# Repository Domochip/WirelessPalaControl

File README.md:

# WPalaControl

This project uses "Palazzetti library" and a D1 Mini to control Fumis based stove.  
It allows to power On/Off, change the setPoint, change fans speed, get status/alarms/temperatures of the stove.

Native HTTP requests are available which make is fully compatible with all existing Palazzetti/Fumis home automation plugins/apps.

Additionally, this project add MQTT protocol to monitor/control your stove in a much more efficient way.

## Stove Compatibility

Fumis Controller is used by many manufacturer for their stoves.
Here is a non-exhaustive list:  
  
Palazzetti / Jotul / TurboFonte / Godin / Fonte Flamme / Invicta / Casatelli / Alpis / Faizen / HETA / ...

If you have this control panel and/or controller in your stove, it's compatible.  

## Home Automation compatibility

|  | [MQTT Integration](https://www.home-assistant.io/integrations/mqtt/) (autodiscovery) |  |
| ------------- | ------------- | ------------- |
|  | [Palazzetti plugin](https://www.jeedom.com/market/index.php?v=d&p=market_display&id=3104) |  |

## Make/Get your adapter

🔧 If you want to build it yourself, you can find all details here : [BUILD](BUILD.md) 🔧  

🛍️🚀 Otherwise, I'm producing some small batches and offering it ready to use here :   

## Connect

⚠️ **You need to use a crossed RJ11 phone cable like this:** ⚠️  

Most of stove have an RJ11/RJ12 connector for PalaControl connection.  
If you don't have it, you need to cable it using a splitter to connect screen and PalaControl at the same time :  

Splitter and additional cable can be found on Aliexpress (search for "6p6c splitter" and "rj12 cable").  
The splitter should correspond to this small schematic :  

## First Boot

During First Boot, the ESP boot in Access Point Mode

- Network SSID : `WirelessPalaControlXXXX`
- Password : `PasswordPalaControl`
- ESP URL : 👉 http://wpalacontrol.local 👈

Connect to this network and then configure it.

## Configuration pages

### Status

It returns you useful informations about the module and the stove.  
**The stove SN appears then 1 minute later, refreshed stove information appears (default upload period)**  

### Config

#### System

- **Reboot**: restart the module
- **Reboot in Rescue Mode**: restart the module with default configuration

#### WiFi

- **ssid & password**: IDs of your Wifi Network  
- **hostname**: name of ESP on the network  
- **IP,GW,NetMask,DNS1&2**: Fixed IP configuration  

#### PalaControl - Home Automation

- **Type**: enable/disable MQTT communication  
- **Upload Period**: delay between refresh of stove information (in seconds)  
- **Hostname,Port,Username,Password**: MQTT server infos (username and password are - optional)  
- **Base Topic**: prefix used for WPalaControl topic structure  
- **MQTT Type**: defines MQTT topics and data structure: 
  - **Generic**: publish raw values under the base topic (e.g. "{baseTopic}/T1" = "*20.00*")
  - **Generic JSON**: publish values JSON to "category" topic under base topic (e.g. "{baseTopic}/TMPS" = "*{"INFO":{"CMD":"GET TMPS","RSP":"OK......*")
  - **Generic Categorized**: publish raw values to "category" topic under base topic (e.g. "{baseTopic}/TMPS/T1" = "*20.00*")
- **Home Assistant Discovery**: Enable/disable Home Assistant auto-discovery

### Firmware

It allows you to flash a new firmware version using `WPalaControl.*.bin` file:  

## Use it

### HTTP

Natively, HTTP GET request can be sent directly to the module.  
Syntax:  **http://wpalacontrol.local/cgi-bin/sendmsg.lua?cmd={command}**

### MQTT

Commands can be sent via MQTT to %BaseTopic%**/cmd** topic once MQTT is configured.  
Execution result is:

- published following the configured MQTT Type
- published on %BaseTopic%**/result** in JSON format 

Module connection status is published to %BaseTopic%**/connected**:

- 0: not connected
- 1: Module connected but no communication with the stove
- 2: Module and stove connected

### Command List
  
- `GET+STDT`: get static data
- `GET+ALLS`: get all status data
- `GET+STAT`: get status of the stove⏲️
- `GET+TMPS`: get temperatures of the stove⏲️
- `GET+FAND`: get Fan values⏲️
- `GET+SETP`: get current Set Point (desired temperature)⏲️
- `GET+POWR`: get current power (1-5)⏲️
- `GET+CUNT`: get some counters
- `GET+CNTR`: get some counters (same as GET+CUNT)⏲️
- `GET+DPRS`: get delta pressure data⏲️
- `GET+TIME`: get stove clock data⏲️
- `GET+IOPT`: get IO ports status
- `GET+SERN`: get stove Serial Number
- `GET+MDVE`: get stove model and fw version
- `GET+CHRD`: get chrono data
- `GET+PARM+92`: get parameter (ex : 92=pellet type (1-3))
- `GET+HPAR+57`: get hidden parameter (ex : 57=% of pellet to feed for pellet type 3)
- `BKP+PARM+CSV`: get all parameters in a CSV file (HTTP only) ✨
- `BKP+PARM+JSON`: get all parameters in a JSON file (HTTP only) ✨
- `BKP+HPAR+CSV`: get all hidden parameters in a CSV file (HTTP only) ✨
- `BKP+HPAR+JSON`: get all hidden parameters in a JSON file (HTTP only) ✨
- `CMD+ON`: turn stove ON
- `CMD+OFF`: turn stove OFF
- `SET+POWR+3`: set power (1-5)
- `SET+PWRU`: increase power by 1 unit
- `SET+PWRD`: decrease power by 1 unit
- `SET+SETP+20`: set Set Point (desired temperature)
- `SET+STPF+19.8`: set Set Point with a 0.2° precision (depend of your stove model)✨
- `SET+STPU`: increase Set Point by 1 unit
- `SET+STPD`: decrease Set Point by 1 unit
- `SET+RFAN+7`: set Room Fan value (0-5;6=Max;7=Auto)
- `SET+FN2U`: increase Room Fan by 1 unit
- `SET+FN2D`: decrease Room Fan by 1 unit
- `SET+FN3L+0`: set Room Fan 3 value (0-5)
- `SET+FN4L+0`: set Room Fan 4 value (0-5)
- `SET+SLNT+0`: set Silent mode value (0-1)
- `SET+TIME+2023-12-28+19:42:00`: set stove Date and Time (2000-2099) (1-12) (1-31) (0-23) (0-59) (0-59)
- `SET+CSST+0`: set Chrono Status value (0-1)
- `SET+CSTH+2+18`: set Chrono Program Start Hour (1-6) (0-23)
- `SET+CSTM+2+30`: set Chrono Program Start Minute (1-6) (0-59)
- `SET+CSPH+2+22`: set Chrono Program Stop Hour (1-6) (0-23)
- `SET+CSPM+2+45`: set Chrono Program Stop Minute (1-6) (0-59)
- `SET+CSET+2+19`: set Chrono Program Set Point (1-6) (desired temperature)
- `SET+CDAY+7+3+6`: set Chrono Program for week day (Day-Mem-Prog) (1-7) (1-3) (1-6)
- `SET+CPRD+1+19+18+30+22+45`: set Chrono Program data (Prog-Temp-StartH-StartM-StopH-StopM) (1-6) (temperature) (0-23) (0-59) (0-23) (0-59)
- `SET+PARM+92+2`: set parameter 92 to value 2 (ex : 92=pellet type (1-3))
- `SET+HPAR+57+95`: set hidden parameter 57 to value 95 (ex : 57=% of pellet to feed for pellet type 3)

⏲️: Published automatically  
✨: WPalaControl specific commands

### Description

MQTT infos published every "Upload Period":

- `STATUS`: status of the stove
- `LSTATUS`: status of the stove
- `T1`, `T2`, `T3`, `T4`, `T5`: temperature of the stove
- `F1V`, `F2V`, `F2L`, `F2LF`, `F3L`, `F4L`: fan values (meaning depend of your stove model)
- `IGN`: ignition counter
- `IGNERRORS`: ignition error counter
- `POWERTIME`: total heating time (hour:minute)
- `HEATTIME`: ??? (hour:minute)
- `SERVICETIME`: heating time since last maintenance (hour:minute)
- `ONTIME`: time from last power ON (hour:minute)
- `OVERTMPERRORS`: overtemperature error counter
- `STOVE_DATETIME`: date of the stove
- `STOVE_WDAY`: week day of the stove
- `SETP`: current Set Point (desired temperature)
- `PQT`: wood pellet consumption
- `PWR`: current power (1-5)
- `FDR`: feeder
- `DP_TARGET`: delta pressure target
- `DP_PRESS`: actual delta pressure

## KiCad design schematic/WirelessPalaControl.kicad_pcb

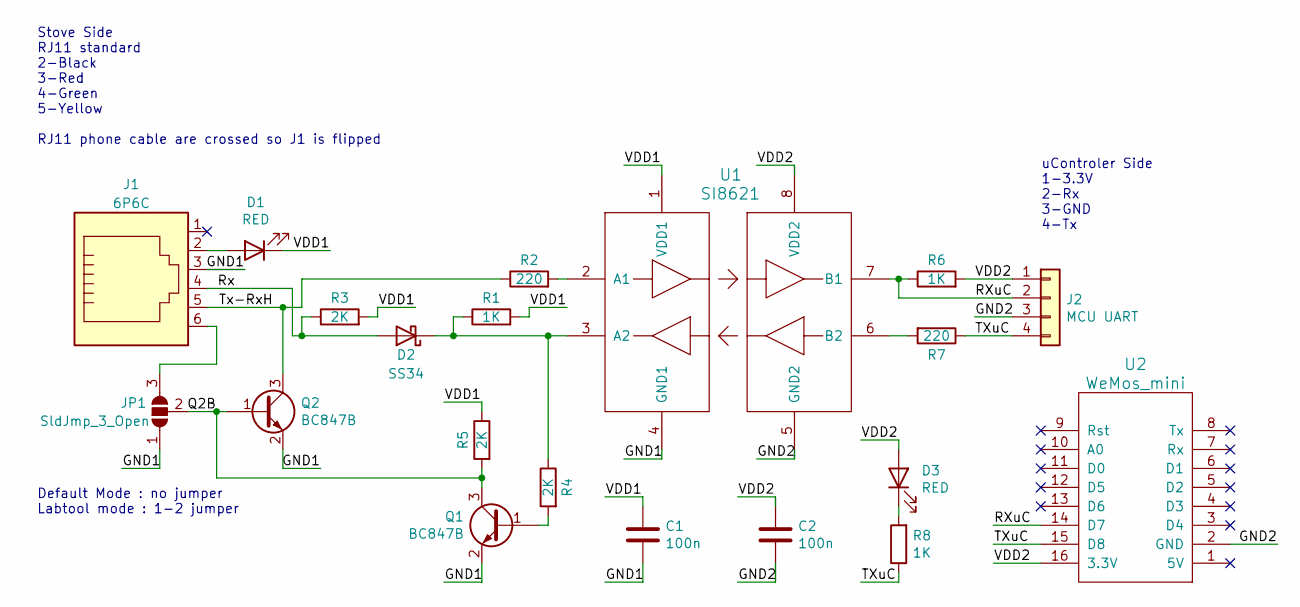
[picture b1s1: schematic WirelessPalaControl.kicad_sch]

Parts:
C1, C2: 100n; C_0805_2012Metric_Pad1.15x1.40mm_HandSolder
D1, D3: RED; LED_0805_2012Metric_Pad1.15x1.40mm_HandSolder
D2: SS34; D_SMA
J1: 6P6C; Ali_RJ12
J2: MCU UART; PinHeader_1x04_P2.54mm_Vertical
JP1: SldJmp_3_Open; SolderJumper-3_P1.3mm_Open_Pad1.0x1.5mm_NumberLabels
Q1, Q2: BC847B; SOT-23_Handsoldering
R1, R6, R8: 1K; R_0805_2012Metric_Pad1.15x1.40mm_HandSolder
R2, R7: 220; R_0805_2012Metric_Pad1.15x1.40mm_HandSolder
R3, R4, R5: 2K; R_0805_2012Metric_Pad1.15x1.40mm_HandSolder
U1: SI8621; SOIC-8_3.9x4.9mm_P1.27mm
U2: WeMos_mini; wemos-d1-mini-DIL-only

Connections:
/GND1: C1.2, J1.3, JP1.1 (A), Q1.2 (E), Q2.2 (E), U1.4 (GND1)
/GND2: C2.2, J2.3, U1.5 (GND2), U2.2 (GND)
/Q2B: JP1.2 (C), Q1.3 (C), Q2.1 (B), R5.2
/RXuC: J2.2, R6.1, U1.7 (B1), U2.14 (D7)
/Rx: D2.2 (A), J1.4, R3.1
/TXuC: J2.4, R7.1, R8.1, U2.15 (D8)
/Tx-RxH: J1.5, Q2.3 (C), R2.1
/VDD1: C1.1, D1.1 (K), R1.2, R3.2, R5.1, U1.1 (VDD1)
/VDD2: C2.1, D3.2 (A), J2.1, R6.2, U1.8 (VDD2), U2.16 (3.3V)
unnamed: D1.2 (A), J1.2
unnamed: D2.1 (K), R1.1, R4.1, U1.3 (A2)
unnamed: D3.1 (K), R8.2
unnamed: J1.6, JP1.3 (B)
unnamed: Q1.1 (B), R4.2
unnamed: R2.2, U1.2 (A1)
unnamed: R7.2, U1.6 (B2)

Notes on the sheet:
uControler Side 1-3.3V 2-Rx 3-GND 4-Tx
Default Mode : no jumper Labtool mode : 1-2 jumper
Stove Side RJ11 standard 2-Black 3-Red 4-Green 5-Yellow RJ11 phone cable are crossed so J1 is flipped

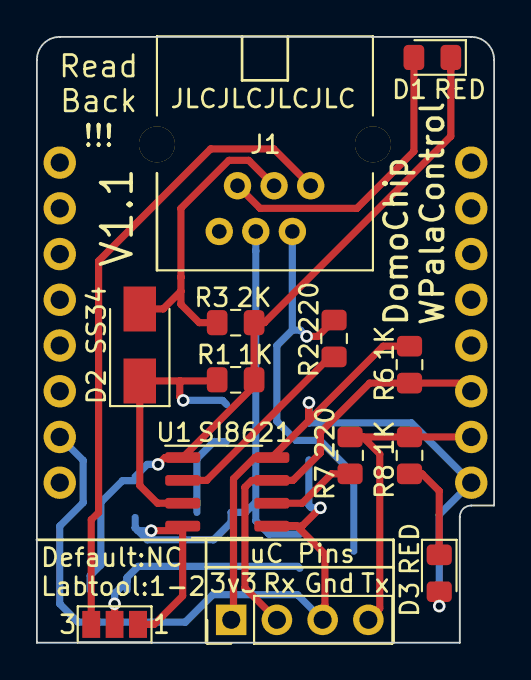
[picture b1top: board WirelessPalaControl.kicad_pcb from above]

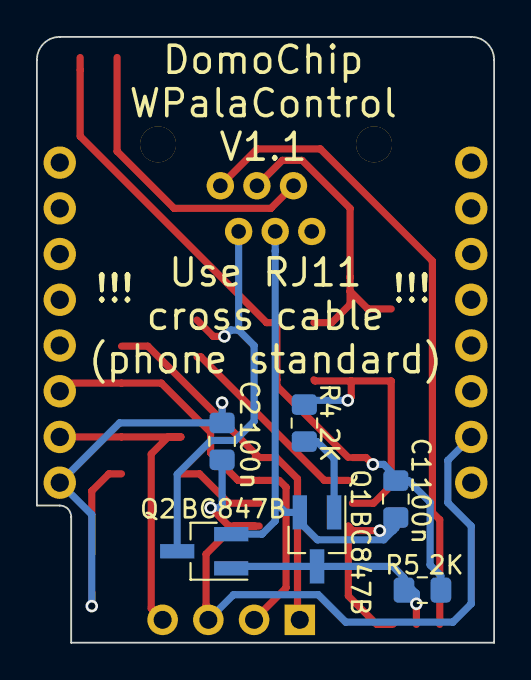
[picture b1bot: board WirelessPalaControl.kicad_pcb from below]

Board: 2 copper layers, 25.4 x 33.7 mm, 20 parts (7 on the bottom side), 16 nets.

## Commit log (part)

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2022-06-20 Add eventSourceOnly param to publishTick()
2022-06-20 split stove reading and MQTT code in publishTick
2022-06-20 Invert event subscription and get status
2022-06-20 improve comment
2022-06-20 Enable publishTicker even without HA
2022-06-20 Invert back event subscription and get status
2022-06-20 Remove eventSourceOnly param to publishTick()
2022-06-20 Add SN during generateStatusJSON()
2022-06-20 Update images
2022-06-20 Bump version to 2.1.1
2023-11-19 Fix version of ArduinoJson lib temporarily
2023-11-19 Ensure correct float rendering
2023-11-19 Use more ArduinoJson in executePalaCmd
2023-11-19 move "cmdProcessed = true"
2023-11-19 Formatting
2023-11-19 move DynJson out of executePalaCmd
2023-11-19 Use AsyncResponseStream to send json back
2023-11-20 return SUCCESS from jsonDoc
2023-11-21 optimize publishTick
2023-11-22 send event to web client in executePalaCmd
2023-11-22 return boolean instead of SUCCESS
2023-11-22 new publishTick using executePalaCmd
2023-11-23 Improved copy_base.py
2023-11-23 Improved prepare_webfiles.py
2023-11-24 comments and rename
2023-11-24 Add publishDataToMqtt method
2023-11-24 write first version of publishDataToMqtt
2023-11-24 use publishDataToMqtt in publishTick
2023-11-25 Add esp8266_exception_decoder
2023-12-03 Add log during init
2023-12-09 Switch LOG_SERIAL to 38400 for simplicity
2023-12-09 Switch monitor_speed to 38400
2023-12-09 Fix Stack issue by passing the whole jsonDoc
2023-12-09 Use the last ArduinoJson library
2023-12-09 Fix GET LABL result
2023-12-09 mqttCallback is able to process any comand
2023-12-09 Add more HA_MQTT type
2023-12-09 HA_MQTT_GENERIC_JSON is now default one
2023-12-09 Add MQTT type to UI
2023-12-10 Factorize publishTick
2023-12-10 publish accordingly to MQTT Generic type
2023-12-12 Add SET TIME comand
2023-12-12 move CMD answer fillin
2023-12-12 Add RSP ERROR answers
2023-12-12 code simplification for GET PARM
2023-12-12 revert code simplification for GET PARM
2023-12-14 Remove .vscode folder
2023-12-14 Ignore the whole .vscode folder
2023-12-16 new WirelessBase files
2023-12-16 Update main.h for new EventSource
2023-12-16 remove libs
2023-12-16 Replace AsyncWebServer by ESP8266WebServer in function definitions
2023-12-17 use new EventSource broadcast function
2023-12-17 adapt parseConfigWebRequest
2023-12-17 appInitWebServer adapted
2023-12-17 Fix getHTMLContent
2023-12-17 Fix incorrect brace
2023-12-17 Format
2023-12-17 WirelessBase Format
2023-12-17 Format web content
2023-12-17 WirelessBase Update
2023-12-17 Improve read of UDP request
2023-12-18 executePalaCmd is publishing and return String
2023-12-19 Switch strings to Flash
2023-12-19 Simplify mySelectSerial
2023-12-19 Memory optimisation (String is heavy)
2023-12-19 switch publishDataToMqtt to if structure for memory
2023-12-19 Simpler MQTT payload reading
2023-12-20 minor optim in mqttCallback and publishDataToMqtt
2023-12-20 reenable list of cmd for publishTick
2023-12-20 Fix missing proper convertion for executePalaCmd return
2023-12-20 not Using FlashString with ArduinoJson saves a LOT of stack
2023-12-20 GET PAR and HPAR result contains number
2023-12-20 last ArduinoJson object named with FlashString
2023-12-20 last ArduinoJson object named with FlashString bis
2023-12-20 publish result to EventSource only for publishTick
2023-12-20 Adjust response headers
2023-12-20 Increase MQTT buffer
2023-12-20 Fix udp Packet reading not working
2023-12-20 comments and move publishTick function
2023-12-21 WirelessBase update V2.0.0
2023-12-26 Implement real Serial flush for ESP8266
2023-12-27 Improve mySelectSerial
2023-12-28 Remove mySelectSerial delay and WDT feed
2023-12-28 Simplify CMD ON/OFF execution
2023-12-28 new executePalaCmd parameters parsing
2023-12-28 GET PARM & HPAR use new parsed params
2023-12-28 SET POWR uses new parsed params
2023-12-28 SET TIME uses new parsed params
2023-12-28 SET RFAN uses new parsed params
2023-12-28 SET FN3L & FN4L use new parsed params
2023-12-28 SET SLNT uses new parsed params
2023-12-28 SET CSST uses new parsed params
2023-12-28 SET CS* use new parsed params
2023-12-28 SET CDAY uses new parsed params
2023-12-28 SET CPRD uses new parsed params
2023-12-28 SET SETP uses new parsed params
2023-12-28 SET STPF uses new parsed params
2023-12-28 SET PARM uses new parsed params
2023-12-28 SET HPAR uses new parsed params
2023-12-28 Raise Incorrect Parameter Value convertion upfront
2023-12-28 return cmd part only for successful execution
2023-12-28 Bump version to 3.0.0
2023-12-28 Fix build on !Windows
    - use / as path separator, not \
    - use proper capitalization for include names
2023-12-29 Fix copy_base.py for !Windows
2023-12-31 Add version to Palazzetti library
2024-01-02 Add STATUS/LSTATUS return to CMD+ON/OFF
2024-01-02 Bump version to 3.0.1
2024-01-02 Fix lib_deps of PlatformIO to target Palazzetti lib tags
2024-01-03 Reorganized Config fields
2024-01-03 Update README images
2024-01-03 Move "PublishTick" Serial print
2024-01-04 Add mqttDisconnectedCallback method
2024-01-04 Add publishStoveConnectedToMqtt method
2024-01-04 Bump version to 3.0.2
2024-01-04 Fix incorrect pattern for MQTT hostname
2024-01-04 change config form id to make it unique
2024-01-04 Use latest Palazzetti Lib
2024-01-04 Stop CountDown if content has changed/reloaded
2024-01-04 Rename variable to Discovery
2024-01-04 Implement publish logic if option enabled and MQTT connected
2024-01-06 Check firmware release on GitHub
2024-01-06 Add function compareVersions
2024-01-07 Add info current and latest fw versions
2024-01-07 Add function for extract fw parts
2024-01-09 Add Base Version header
2024-01-09 Implement Connectivity entities
2024-01-09 Add Serial Log of publishHassDiscoveryToMqtt
2024-01-10 publishTick after Hass publish
2024-01-10 move some variables
2024-01-10 Change Stove device information
2024-01-10 Add Status entity
2024-01-10 Add availability for Stove entities
2024-01-10 Add SetPoint Entity
2024-01-10 Add Power entity
2024-01-10 Add OnOff entity
2024-01-11 Add Status Text entity
2024-01-13 add padZero
    To add zero on <10 numbers
2024-01-13 Add OTA firmware
    Check firmware online, and OTA online if version is below
2024-01-14 Add GitHub auto compilation&release
2024-01-19 Add RSSI in select configw
2024-01-19 Add RSSI in /wnl
2024-01-26 Use new Palazzetti lib CommandResult
2024-01-27 Create mn0.html
    Monitor page
2024-01-27 Update index.html
    Add monitor page
2024-01-27 Update Application.cpp
    Add monitor page
2024-01-27 Add monitor page
2024-01-27 Update Core.cpp
    Add monitor page
2024-01-27 Update Core.h
    Add monitor page
2024-01-28 Hide name cmd on small screen device
2024-01-30 Use new Palazzetti lib version
2024-01-31 Keep only used StaticData
2024-02-03 comment
2024-02-03 Add RoomFan entity
2024-02-03 Add RoomFan Auto entity
2024-02-03 Add Fan3 entity
2024-02-03 Add Fan4 entity
2024-02-03 Add Pellet consumption entity
2024-02-03 Add Room temperature entity
2024-02-03 Fix wrong topic
2024-02-03 Bump version to 3.1.0
2024-02-03 Adapt code for ArduinoJson7
2024-02-03 Bump version to 3.1.1
2024-02-03 Remove unused variables
2024-02-03 Bump version to 3.1.2
2024-02-03 Return new Palazzetti lib version
2024-02-03 Add missing DSPTYPE
2024-02-03 Fix Categorized publishing
2024-02-03 HomeAssistant MQTT Discovery enabled only for Generic publishing
2024-02-03 Fix icon of Room fan in HASS
2024-02-03 Remove Discover chapter in README.md
2024-02-04 Use newest Palazzetti lib
2024-02-06 Adapt publishHassDiscoveryToMqtt for other publish types
2024-02-09 Retrieve FANLMINMAX
2024-02-09 Adjust Hass entity type for F3 and F4
2024-02-10 Sort hass entities per type
2024-02-11 Fix Hass wrong Power topic
2024-09-01 Remove unused PolledTimeout lib
2024-09-01 Add platformio esp32 platform
2024-09-01 Replace server.keepAlive(false); with SERVER_KEEPALIVE_FALSE() macro
2024-09-01 Adapt publishTicker attach
2024-09-01 Adjust udp write
2024-09-02 Replace polledTimeout code
2024-09-02 adapt LOG_SERIAL for ESP32
2024-09-02 Draft of Serial mgmt for ESP32
2024-09-04 Update comments
2024-09-04 Now using publish Palazzetti lib
2024-09-04 use latest Palazzetti lib version
2024-09-07 Configure D1Mini as default env for PlatformIO
2024-09-07 Remove monitor_port
2024-09-07 Bump version to 3.1.3
2024-09-08 Add release badge
2024-09-08 Add Home Assistant logo
2024-09-08 Fix MarkDown issues
2024-09-08 Update configMQTT.png image
2024-09-10 add complete-module img
2024-09-10 Add tindie img
2024-09-11 use same lib names
2024-09-11 Rename the GHAction
2024-09-11 only manually triggered for now
2024-09-11 Update preparation steps
2024-09-11 Add VERSION variable
2024-09-11 Update Release generation
2024-09-11 Rename firmware file
2024-09-11 Reorder steps
2024-09-11 Add missing permissions
2024-09-11 use newest action and set as draft
2024-09-11 wording
2024-09-11 Add GitHub auto compilation&release (#27)
    * Add GitHub auto compilation&release
    * Update main.yml
    * Create main.yml
    * Delete .github/workflows directory
    * Update main.yml
    * Rename the GHAction
2024-09-12 Remove SNCHK control because of manufacturer not setting proper SN
2024-09-12 Bump version to 3.1.4
2024-09-13 factorize wifi option JS code
2024-09-13 RSSI is a number
2024-09-13 change rssi to quality
2024-09-13 Add color to options
2024-09-13 Add Quality in select on configw page (#28)
    * Add RSSI in select configw
    * Add RSSI in /wnl
    * Update configw.html
    * factorize wifi option JS code
    * RSSI is a number
    * change rssi to quality
2024-09-24 factorize platformio.ini config
2024-09-24 Adjust Fan presence order
2024-09-25 Fix bad topic in HA autodiscovery
2024-09-25 Improve return of some SET commands on MQTT
2024-09-25 define correct return target topic for SET commands
2024-09-25 Improve config JSON content tests
2024-09-25 Use JsonDocument for WPalaControl config
2024-09-25 Use JsonDocument for WPalaControl status
2024-09-25 Use JsonDocument for Json typed BKP commands
2024-09-25 Minor codeline reordering
2024-09-25 Improve parseConfigJSON
2024-09-27 If stove status is 10 (Fire Stop), it should be considered OFF
2024-09-27 remove flash string in Json lookup
2024-09-27 Optimize memory before serializing result of palaCmd
2024-09-28 Increase ESP32 upload speed
2024-09-28 Change parseConfigJSON signature
2024-09-28 Switch to JSON post for config
2024-09-28 Bump version to 3.1.5
2024-09-29 Define ArduinoJson lib version
2024-09-29 Clean bad comment
2024-09-29 Reorder AppRun actions to avoid double publishTick
2024-09-29 Improve serialization performance for big Json
2024-10-01 Simplify Version number sent to Home Assistant
2024-10-01 Publish WPalaControl connectivity to Home Assistant even without stove
2024-10-01 Adjust Github Action for new versioning
2024-10-01 Adapt code for Base 2.3.3
2024-10-01 Bump version to 3.1.6
2024-10-03 Create Browser EventSource only if doesn't exists yet or is disconnected
2024-10-03 Move preventDefault in config1.html
2024-10-06 Bump version to 3.1.7
2024-10-08 Reorder PalaCommand in alphabetical order
2024-10-08 Add EXT ADRD pala command
2024-10-08 Add EXT ADWR command commented out
2024-10-08 command EXT ADWR available only in Developer mode
2024-10-08 Palazzetti lib update to 2.7.4
2024-10-08 Bump version to 3.1.8
2024-10-12 Adapt for the new EventSource class
2024-10-12 Adapt for the new EventSource class (#52)
2024-10-12 Bump version to 3.1.9
2024-10-16 Reduce hassDiscoveryPrefix from 64 to 32 chars
2024-10-16 Reduce mqtt username from 128 to 32 chars
2024-10-16 Reduce mqtt password from 150 to 64 chars
2024-10-16 Bump version to 3.1.10
2024-10-19 Update schematic to KiCAD8
2024-10-19 Add gitignore for KiCad
2024-10-19 Update gitignore
2024-10-19 Adapt for Base 2.3.9
2024-10-19 Send module infos to MQTT baseTopic
2024-10-20 Use _appName for MQTT status reporting
2024-10-20 Improve WPalaControl status
2024-10-20 Optimization
2024-10-21 Bump version to 3.1.11
2024-10-21 Rename WebPalaControl class to WPalaControl
2024-10-21 Rename files from WirelessPalaControl to WPalaControl
2024-10-21 Change appName in webpage
2024-10-21 Change firmware name to WPalaControl
2024-10-21 Adapt code for Base 2.3.11
2024-10-21 Update copy_base.py script
